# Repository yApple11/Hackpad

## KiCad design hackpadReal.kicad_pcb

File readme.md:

# hackpad

*A short description of the keyboard/project*

* Keyboard Maintainer: [yaseen baladi](https://github.com/yApple11)
* Hardware Supported: *The PCBs, controllers supported*
* Hardware Availability: *Links to where you can find this hardware*

Make example for this keyboard (after setting up your build environment):

    make hackpad:default

Flashing example for this keyboard:

    make hackpad:default:flash

See the [build environment setup](https://docs.qmk.fm/#/getting_started_build_tools) and the [make instructions](https://docs.qmk.fm/#/getting_started_make_guide) for more information. Brand new to QMK? Start with our [Complete Newbs Guide](https://docs.qmk.fm/#/newbs).

## Bootloader

Enter the bootloader in 3 ways:

* **Bootmagic reset**: Hold down the key at (0,0) in the matrix (usually the top left key or Escape) and plug in the keyboard
* **Physical reset button**: Briefly press the button on the back of the PCB - some may have pads you must short instead
* **Keycode in layout**: Press the key mapped to `QK_BOOT` if it is available

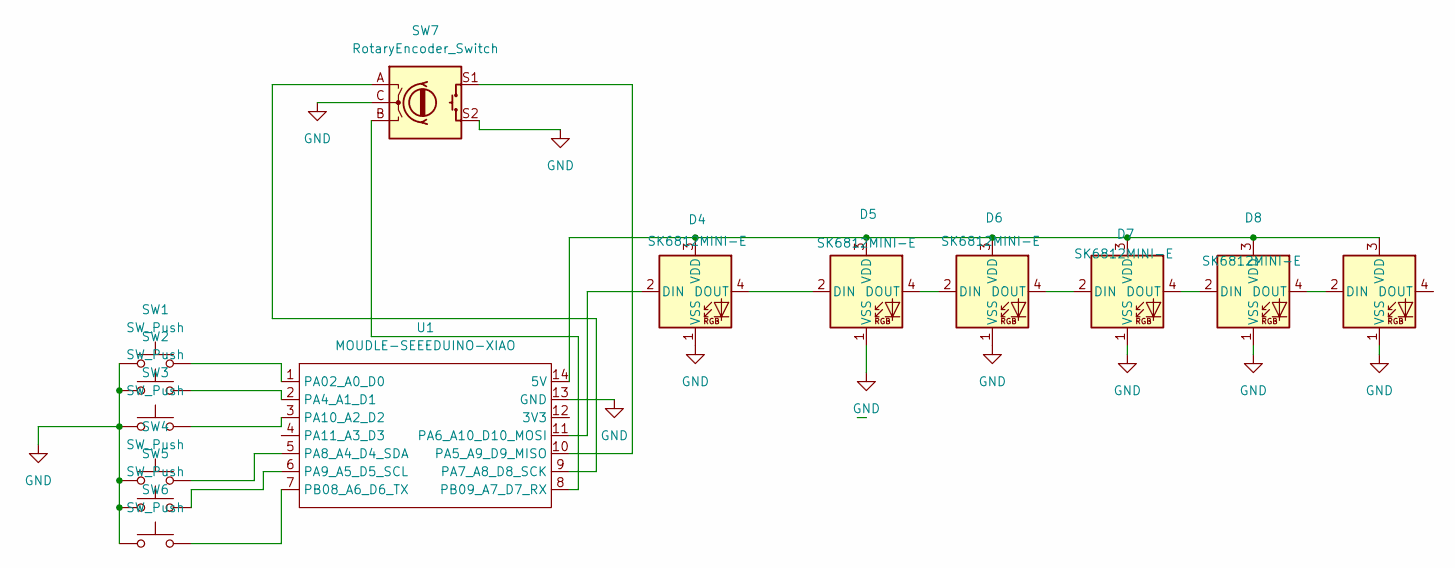
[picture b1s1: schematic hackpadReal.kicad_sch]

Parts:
D4, D5, D6, D7, D8, D9: SK6812MINI-E; LED_SK6812MINI-E_3.2x2.8mm_P1.5mm_ReverseMount
SW1, SW2, SW3, SW4, SW5, SW6: SW_Push; SW_Cherry_MX_1.00u_PCB
SW7: RotaryEncoder_Switch; RotaryEncoder_Alps_EC11E-Switch_Vertical_H20mm
U1: MOUDLE-SEEEDUINO-XIAO; XIAO-Generic-Hybrid-14P-2.54-21X17.8MM

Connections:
GND: D4.1 (VSS), D5.1 (VSS), D6.1 (VSS), D7.1 (VSS), D8.1 (VSS), D9.1 (VSS), SW1.1, SW2.1, SW3.1, SW4.1, SW5.1, SW6.1, SW7.C, SW7.S2, U1.13 (GND)
unnamed: D4.2 (DIN), U1.11 (PA6_A10_D10_MOSI)
unnamed: D4.4 (DOUT), D5.2 (DIN)
unnamed: D4.3 (VDD), D5.3 (VDD), D6.3 (VDD), D7.3 (VDD), D8.3 (VDD), D9.3 (VDD), U1.14 (5V)
unnamed: D5.4 (DOUT), D6.2 (DIN)
unnamed: D6.4 (DOUT), D7.2 (DIN)
unnamed: D7.4 (DOUT), D8.2 (DIN)
unnamed: D8.4 (DOUT), D9.2 (DIN)
unnamed: SW1.2, U1.1 (PA02_A0_D0)
unnamed: SW2.2, U1.2 (PA4_A1_D1)
unnamed: SW7.S1, U1.10 (PA5_A9_D9_MISO)
unnamed: SW7.A, U1.9 (PA7_A8_D8_SCK)
unnamed: SW4.2, U1.5 (PA8_A4_D4_SDA)
unnamed: SW5.2, U1.6 (PA9_A5_D5_SCL)
unnamed: SW3.2, U1.3 (PA10_A2_D2)
unnamed: SW6.2, U1.7 (PB08_A6_D6_TX)
unnamed: SW7.B, U1.8 (PB09_A7_D7_RX)

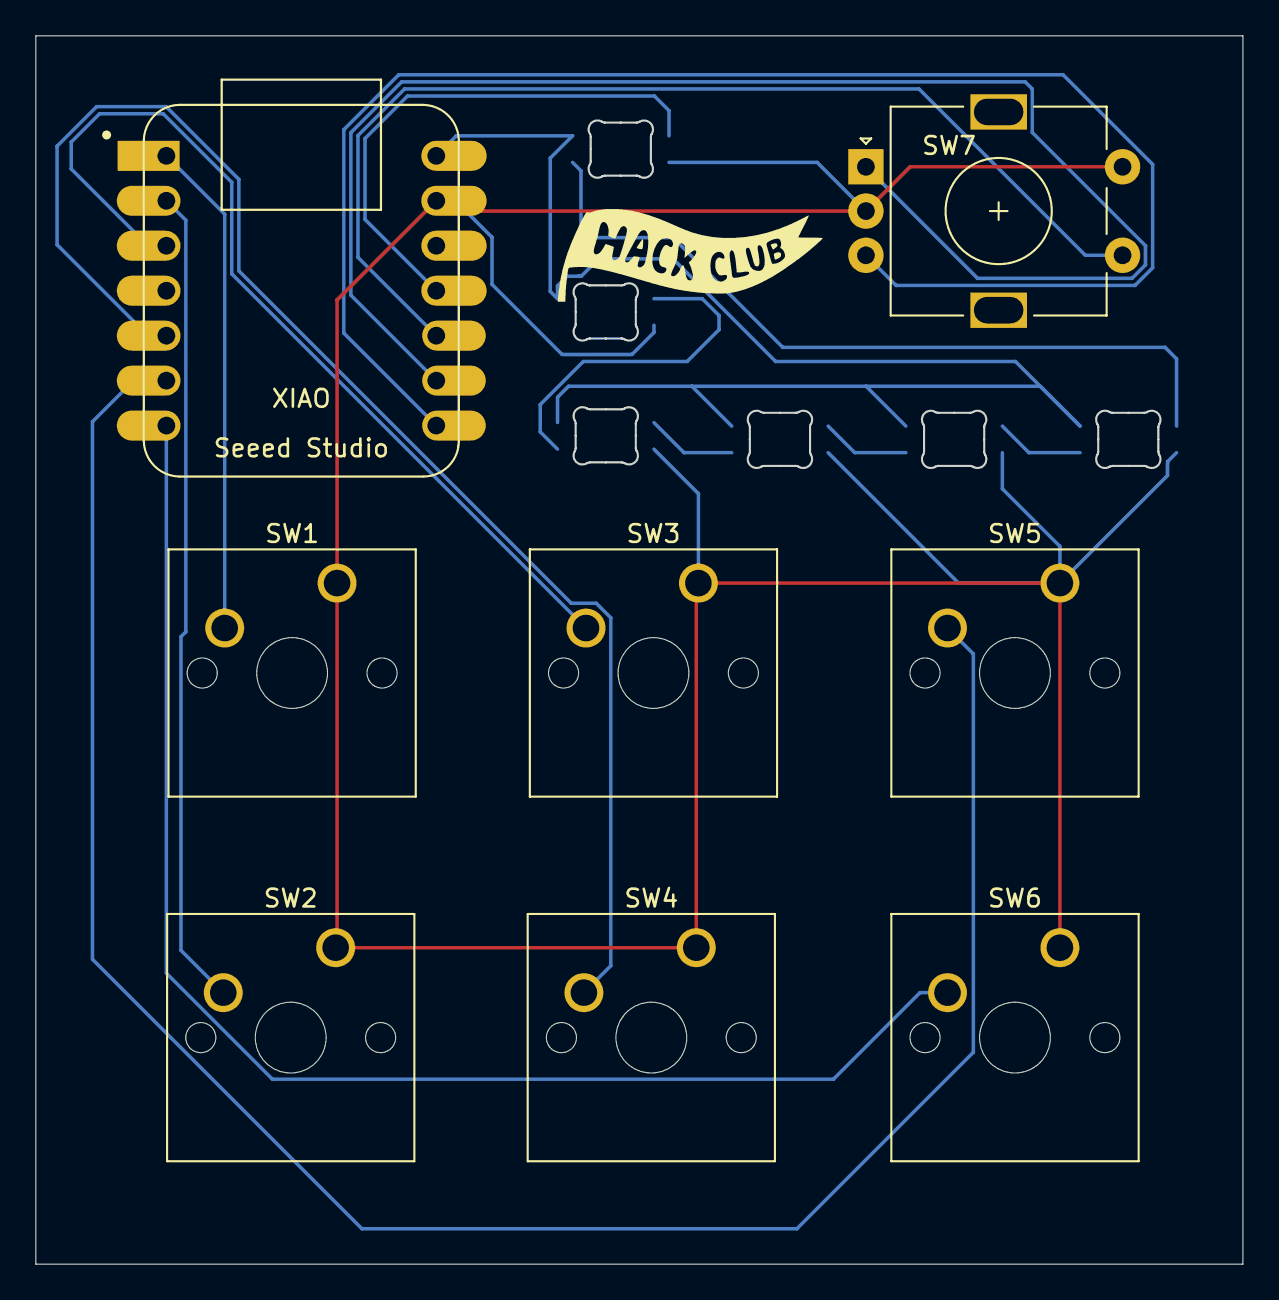
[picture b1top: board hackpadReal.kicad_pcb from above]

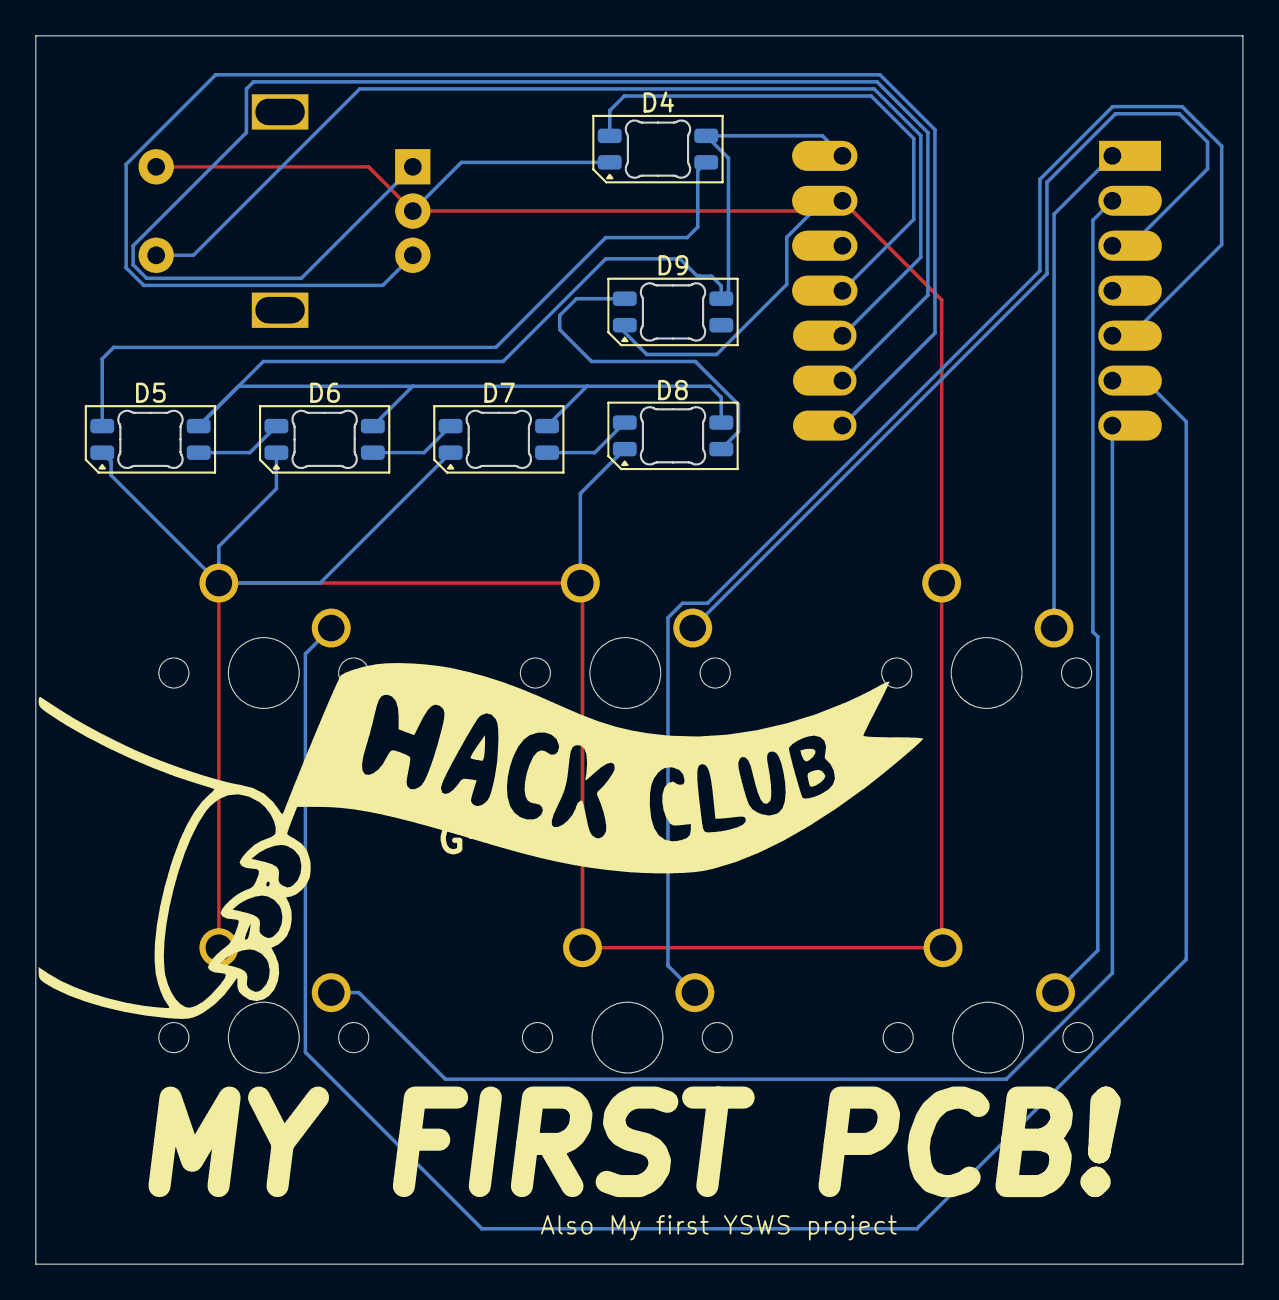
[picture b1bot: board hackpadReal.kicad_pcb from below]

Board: 2 copper layers, 68.2 x 69.4 mm, 14 parts (6 on the bottom side), 17 nets.
